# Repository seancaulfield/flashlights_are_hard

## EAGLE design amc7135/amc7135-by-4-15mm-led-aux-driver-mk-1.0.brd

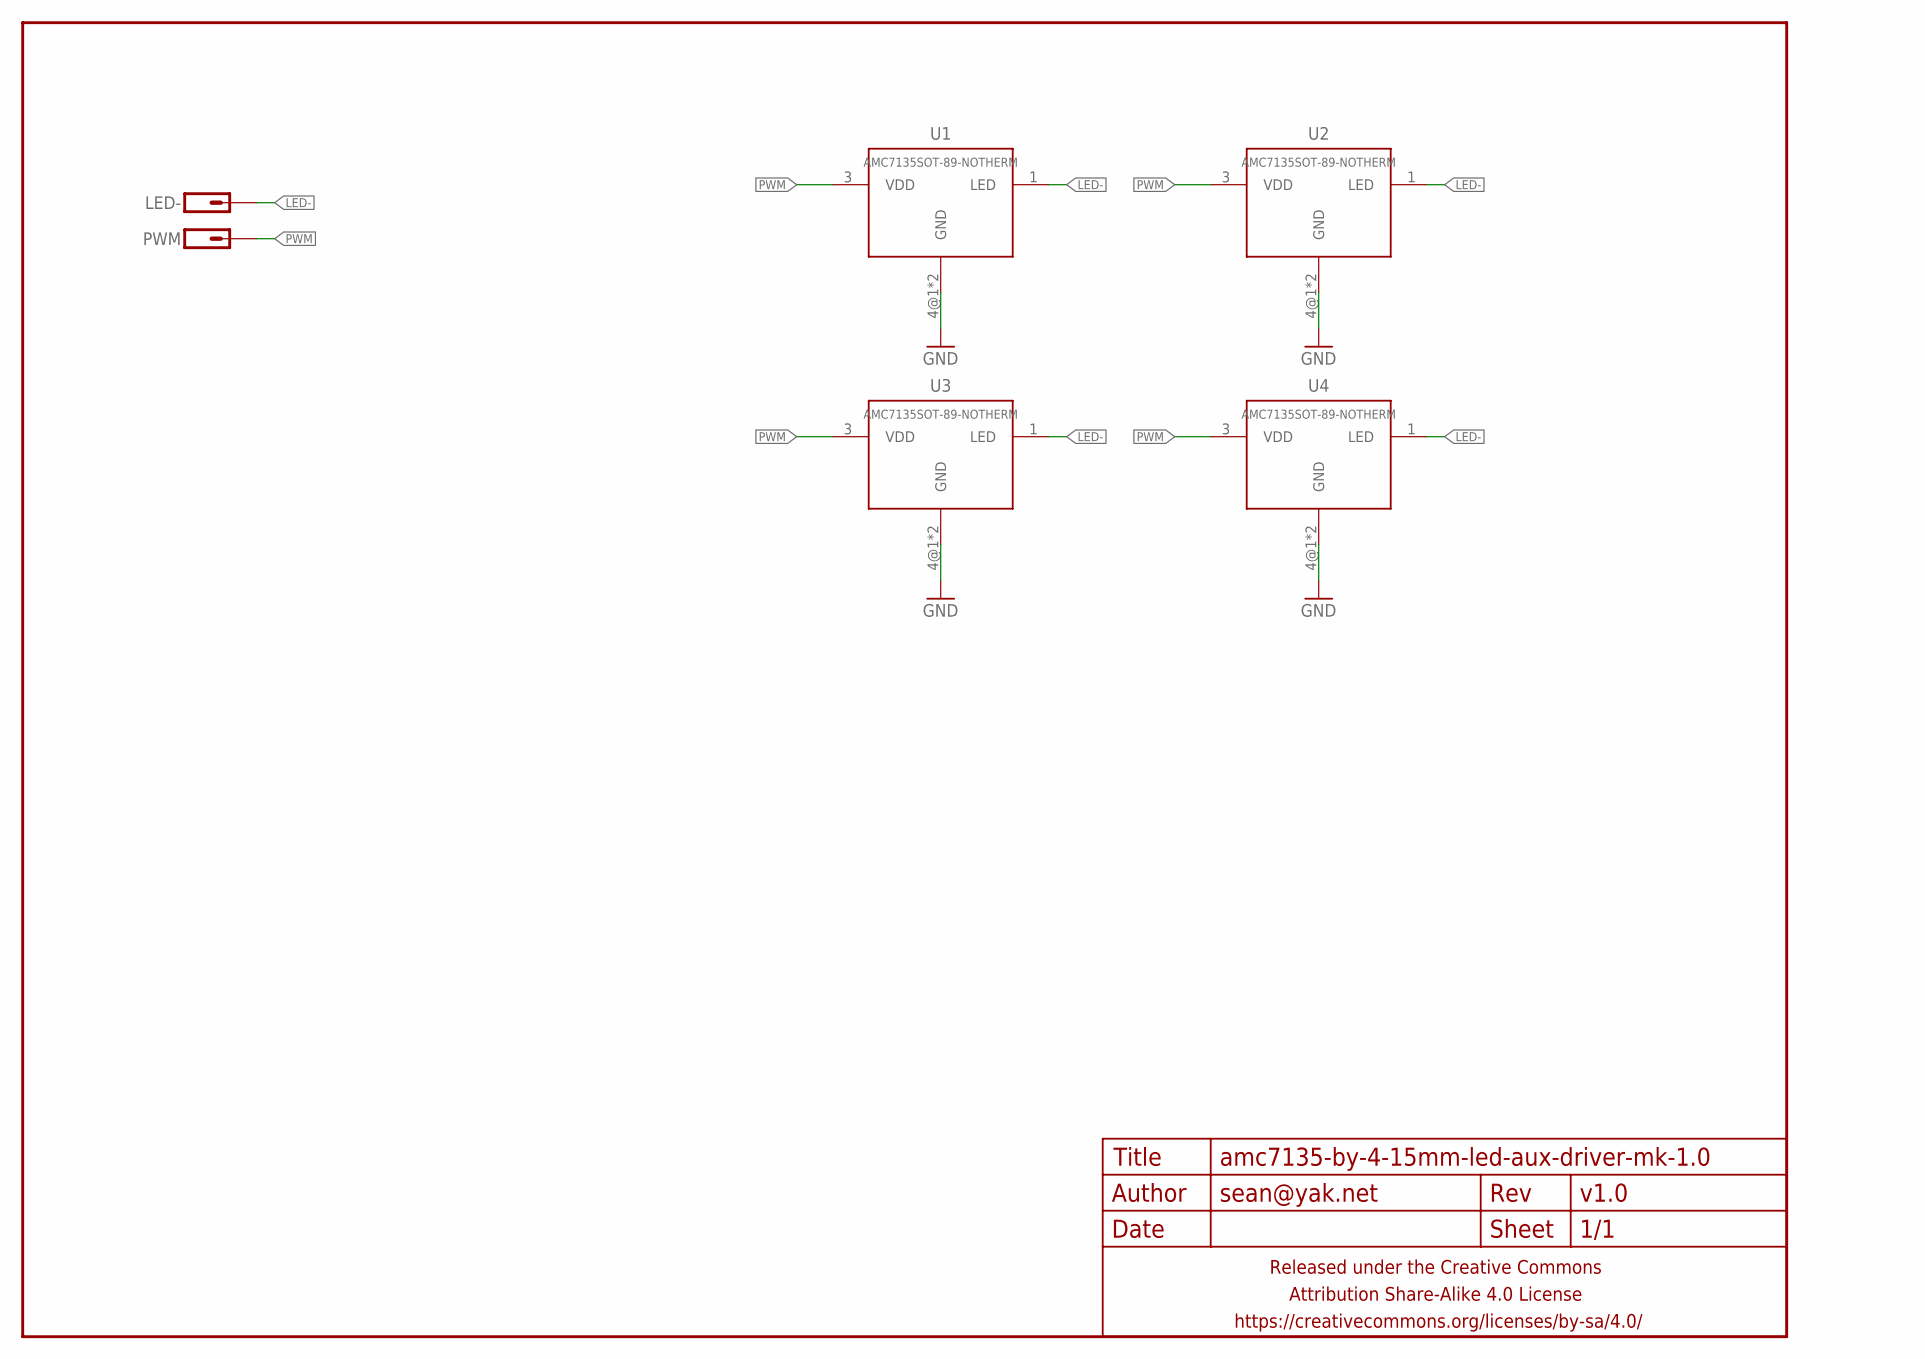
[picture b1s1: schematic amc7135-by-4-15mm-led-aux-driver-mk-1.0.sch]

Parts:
FRAME1: FRAME-LETTERNO_PACKAGE; DUMMY
LED-: M01SMD-1.25MM-DIA; 1X01-SMD-1.25MM-DIA-NS
PWM: M01SMD-1.25MM-DIA; 1X01-SMD-1.25MM-DIA-NS
U1, U2, U3, U4: AMC7135SOT-89-NOTHERM; SOT89-NOTHERM

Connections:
GND: U1.4@1 (GND), U1.4@2 (GND), U2.4@1 (GND), U2.4@2 (GND), U3.4@1 (GND), U3.4@2 (GND), U4.4@1 (GND), U4.4@2 (GND)
LED-: LED-.P$1, U1.1 (LED), U2.1 (LED), U3.1 (LED), U4.1 (LED)
PWM: PWM.P$1, U1.3 (VDD), U2.3 (VDD), U3.3 (VDD), U4.3 (VDD)

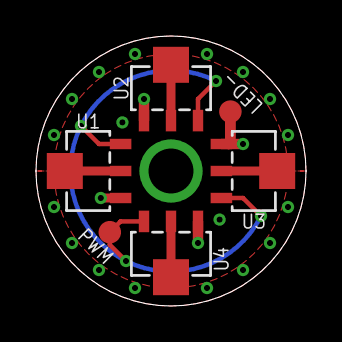
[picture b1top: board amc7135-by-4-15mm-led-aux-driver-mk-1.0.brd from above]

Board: 2 copper layers, 15.0 x 15.0 mm, 7 parts (0 on the bottom side), 3 nets.

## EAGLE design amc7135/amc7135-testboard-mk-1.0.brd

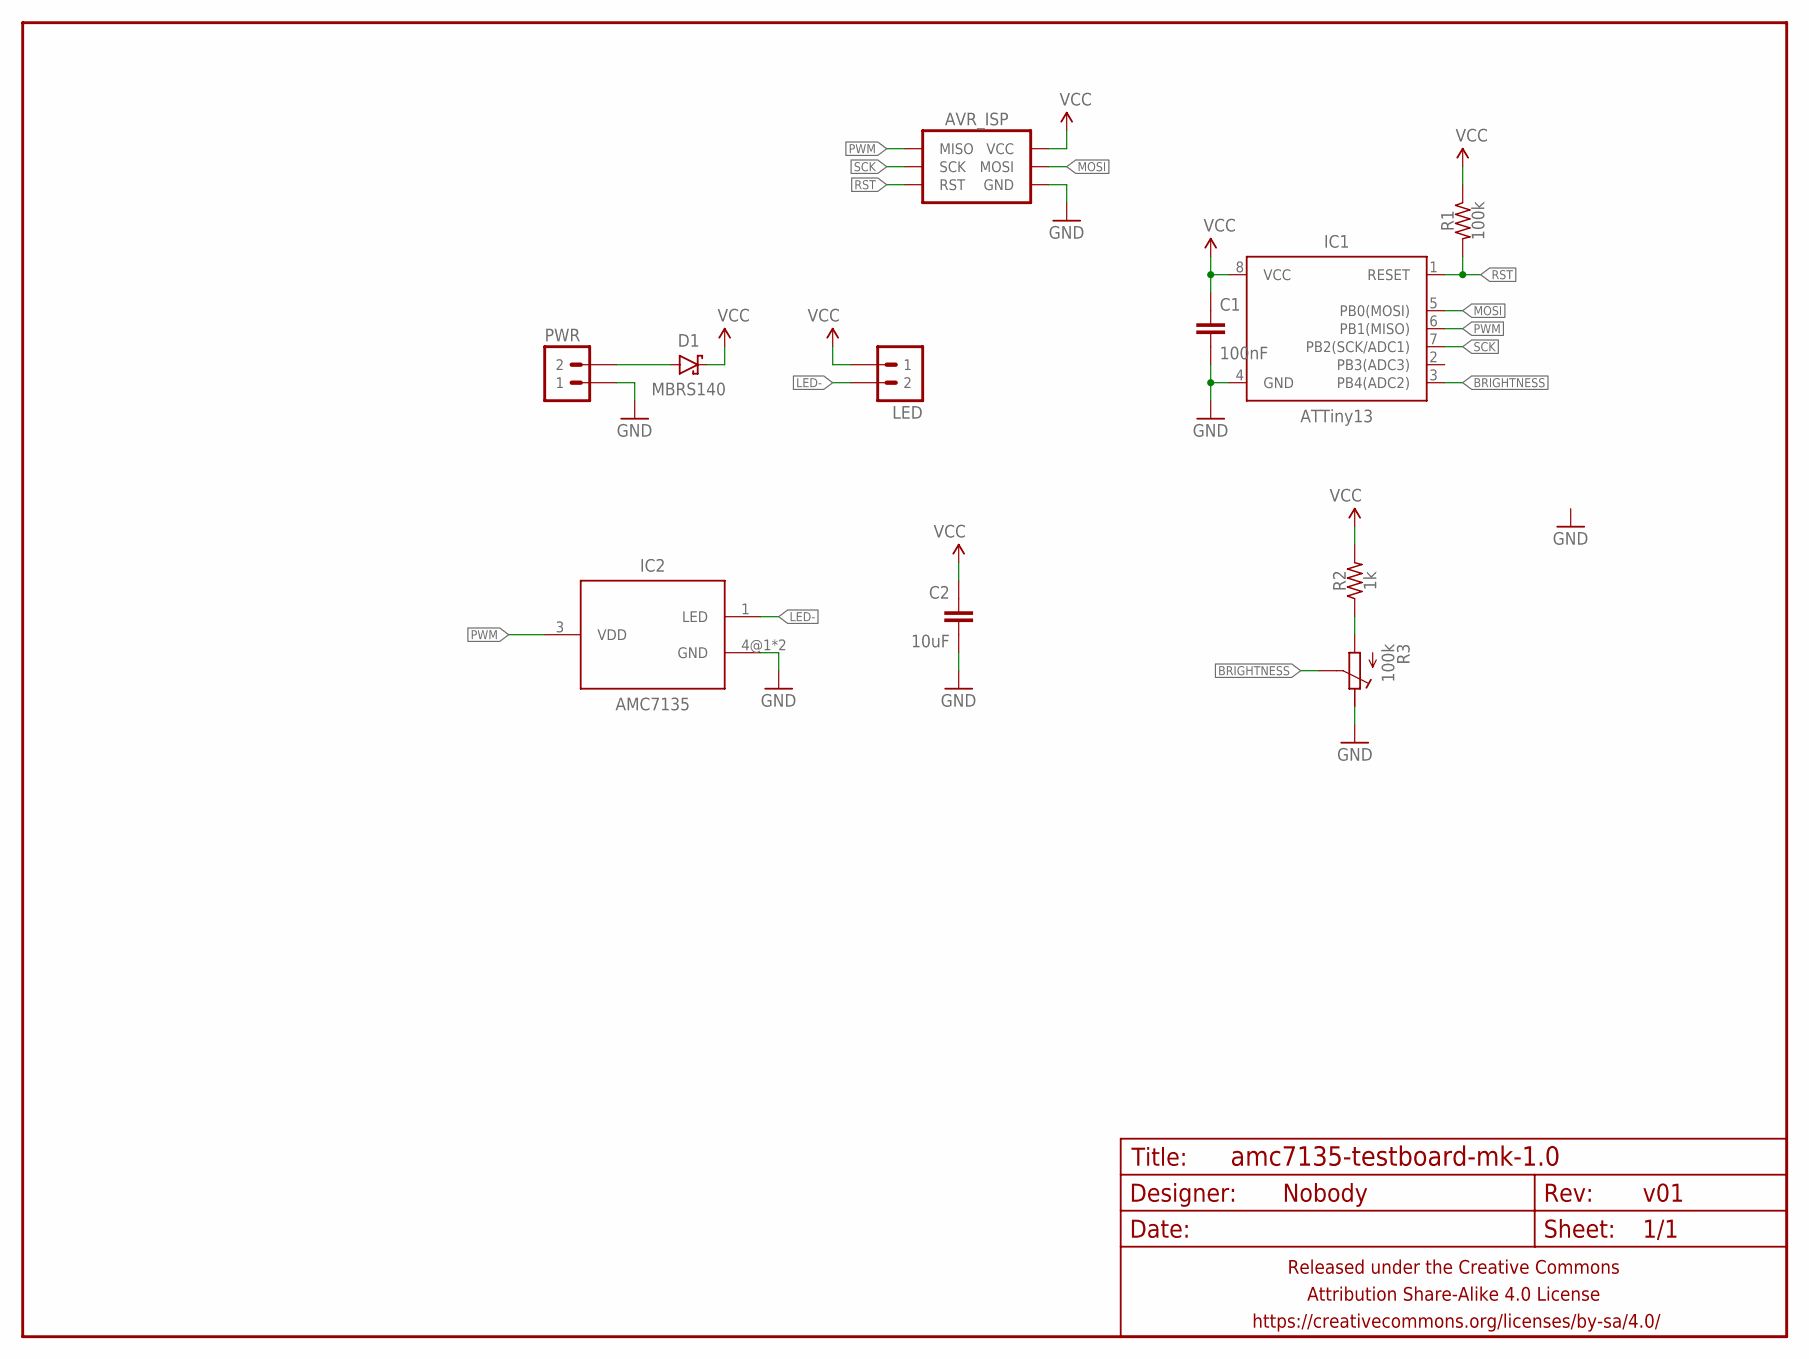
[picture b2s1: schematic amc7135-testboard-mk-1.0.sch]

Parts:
AVR_ISP: AVR_SPI_PRG_6SMD_TEST_POINTS; 2X3_SMD_TEST_POINTS
C1: 100nF; C0805
C2: 10uF; C0805
D1: MBRS140; SMA-DIODE-SCHOTTKY
FRAME1: FRAME-LETTERNO_PACKAGE; DUMMY
IC1: ATTiny13; SO08
IC2: AMC7135; SOT89-NOTHERM
LED: M02JST-PTH-RA-SMALLPADS; JST-2-PH-RA-PTH-SMALLPADS
PWR: M02JST-PTH-RA-SMALLPADS; JST-2-PH-RA-PTH-SMALLPADS
R1: 100k; R0805
R2: 1k; R0805
R3: 100k; EVM3Y

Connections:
BRIGHTNESS: IC1.3 (PB4(ADC2)), R3.S
GND: AVR_ISP.6 (GND), C1.2, C2.2, IC1.4 (GND), IC2.4@1 (GND), IC2.4@2 (GND), PWR.1, R3.E
LED-: IC2.1 (LED), LED.2
MOSI: AVR_ISP.4 (MOSI), IC1.5 (PB0(MOSI))
unnamed: R2.1, R3.A
unnamed: D1.A, PWR.2
PWM: AVR_ISP.1 (MISO), IC1.6 (PB1(MISO)), IC2.3 (VDD)
RST: AVR_ISP.5 (RST), IC1.1 (RESET), R1.2
SCK: AVR_ISP.3 (SCK), IC1.7 (PB2(SCK/ADC1))
VCC: AVR_ISP.2 (VCC), C1.1, C2.1, D1.C, IC1.8 (VCC), LED.1, R1.1, R2.2

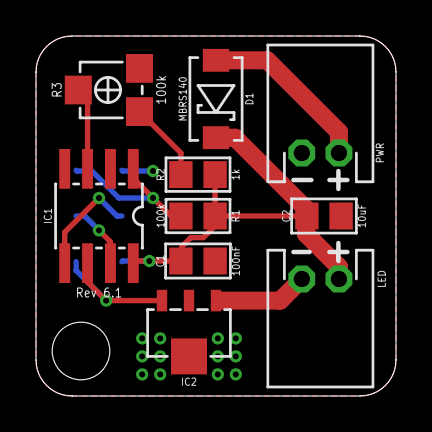
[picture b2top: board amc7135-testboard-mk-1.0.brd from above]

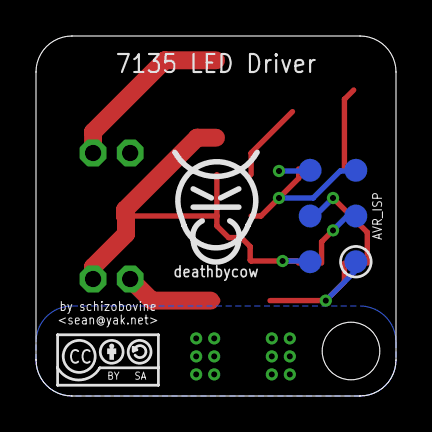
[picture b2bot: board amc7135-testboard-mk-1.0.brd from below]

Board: 2 copper layers, 20.0 x 20.0 mm, 14 parts (3 on the bottom side), 10 nets.

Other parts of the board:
U$1: CC-BY-SA-4.0-NO-URL
U$2: COW_SMALL

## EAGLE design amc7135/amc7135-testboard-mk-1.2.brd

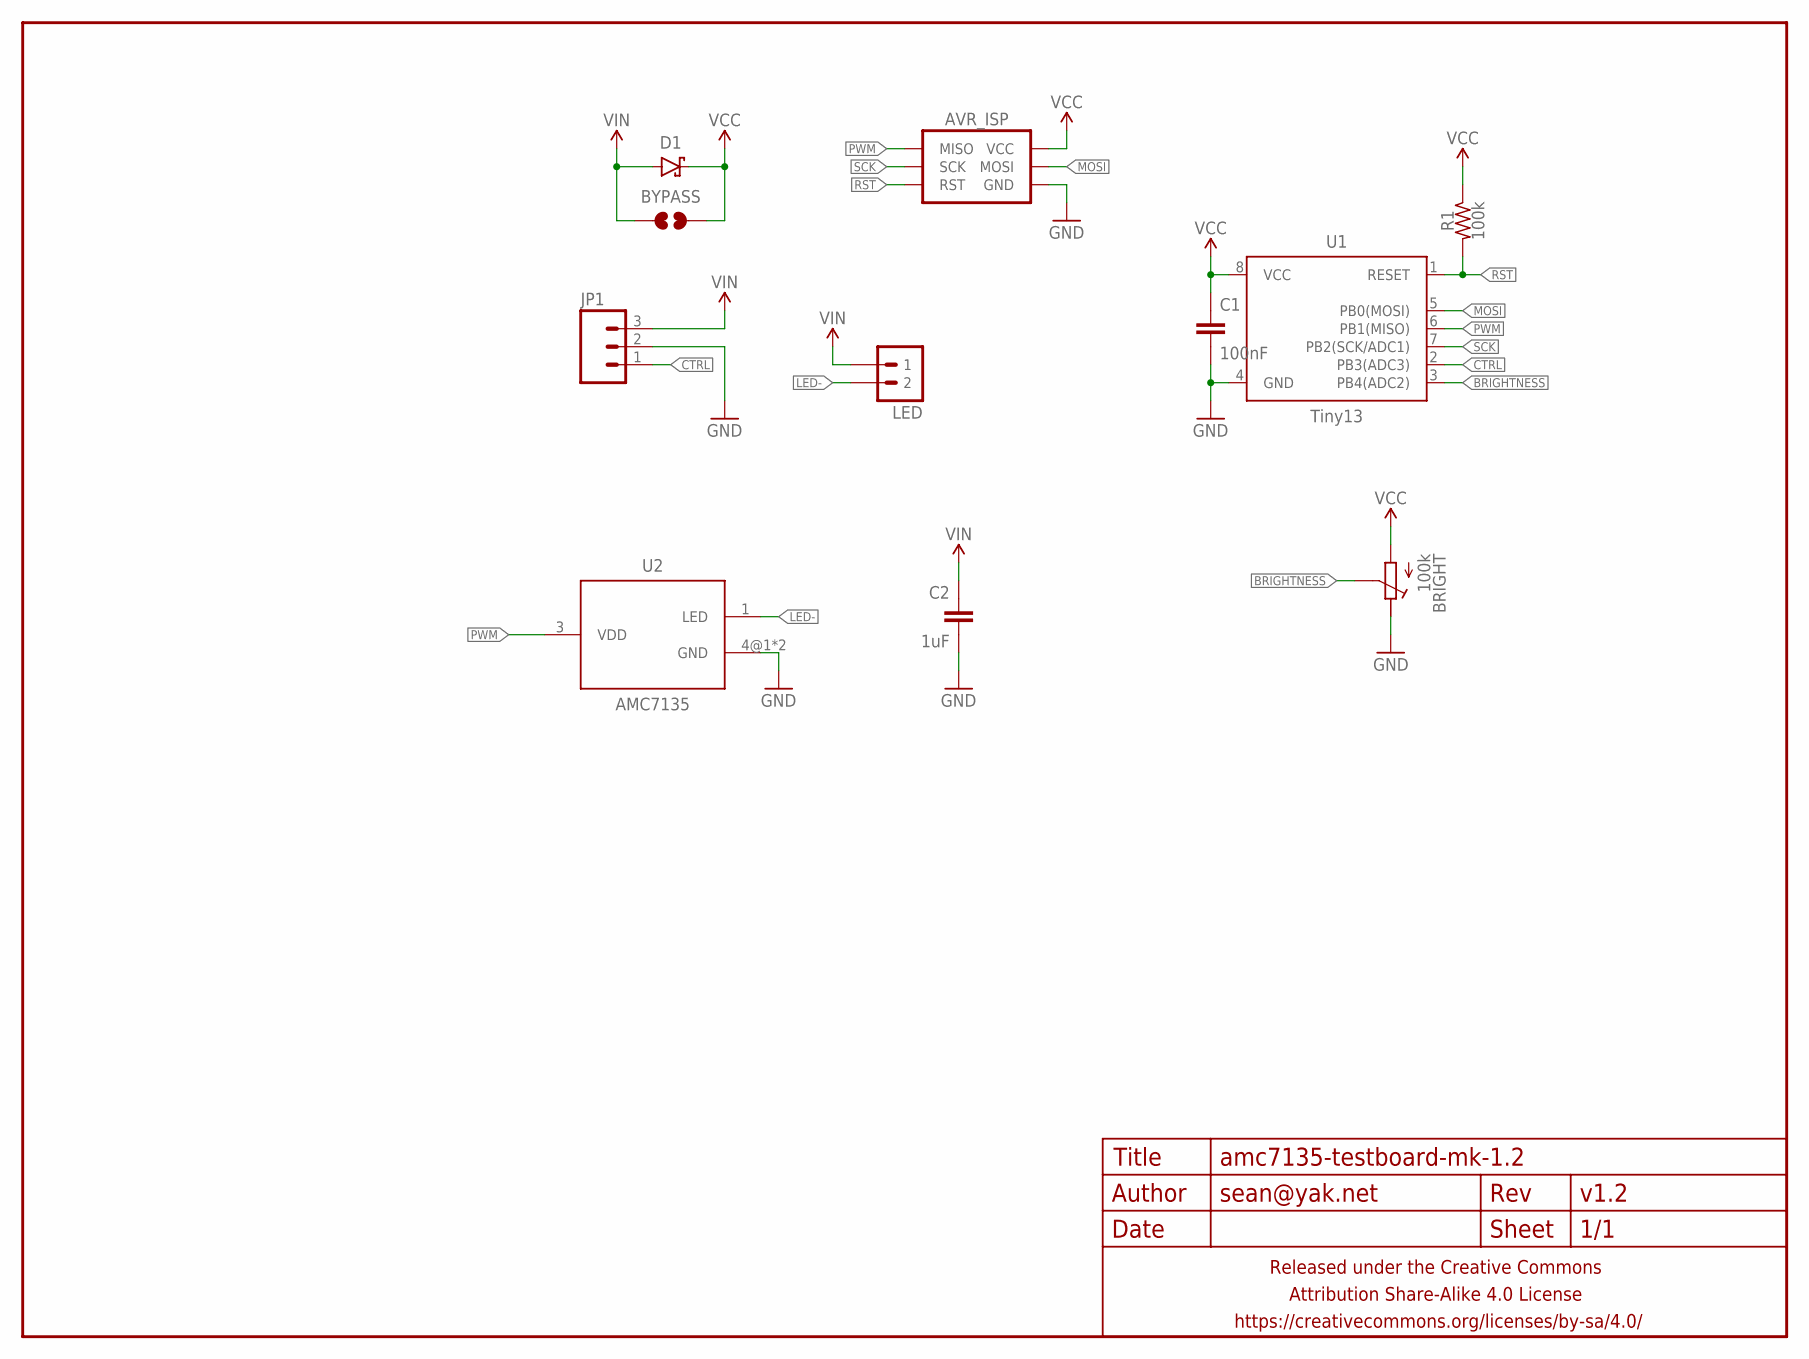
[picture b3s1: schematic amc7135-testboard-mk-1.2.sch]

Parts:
AVR_ISP: AVR_SPI_PRG_6SMD_TEST_POINTS; 2X3_SMD_TEST_POINTS
BRIGHT: 100k; EVM3Y
BYPASS: JUMPER-PAD-2-NOYES_SILK; PAD-JUMPER-2-NO_YES_SILK
C1: 100nF; C0603-TIGHTER
C2: 1uF; C0603-TIGHTER
D1: DIODE-SCHOTTKYSOD323; SOD323-SCHOTTKY
FRAME1: FRAME-LETTERNO_PACKAGE; DUMMY
JP1: M03PTH-CENTERED; 1X03-CENTERED
LED: M02PTH-CENTERED; 1X02-CENTER
R1: 100k; R0603-TIGHTER
U1: Tiny13; SO08
U2: AMC7135; SOT89-NOTHERM

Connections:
BRIGHTNESS: BRIGHT.S, U1.3 (PB4(ADC2))
CTRL: JP1.1, U1.2 (PB3(ADC3))
GND: AVR_ISP.6 (GND), BRIGHT.E, C1.2, C2.2, JP1.2, U1.4 (GND), U2.4@1 (GND), U2.4@2 (GND)
LED-: LED.2, U2.1 (LED)
MOSI: AVR_ISP.4 (MOSI), U1.5 (PB0(MOSI))
PWM: AVR_ISP.1 (MISO), U1.6 (PB1(MISO)), U2.3 (VDD)
RST: AVR_ISP.5 (RST), R1.2, U1.1 (RESET)
SCK: AVR_ISP.3 (SCK), U1.7 (PB2(SCK/ADC1))
VCC: AVR_ISP.2 (VCC), BRIGHT.A, BYPASS.2, C1.1, D1.C, R1.1, U1.8 (VCC)
VIN: BYPASS.1, C2.1, D1.A, JP1.3, LED.1

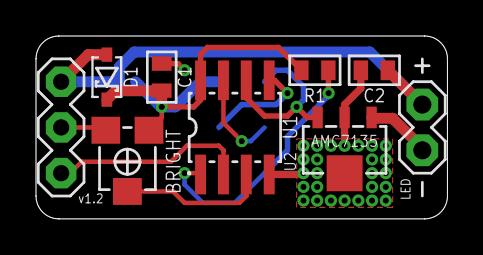
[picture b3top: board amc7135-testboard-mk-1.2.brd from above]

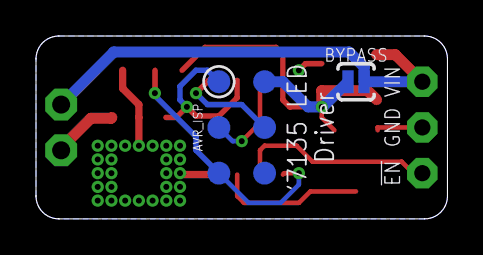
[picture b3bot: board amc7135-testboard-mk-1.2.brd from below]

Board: 2 copper layers, 22.9 x 10.2 mm, 12 parts (2 on the bottom side), 10 nets.

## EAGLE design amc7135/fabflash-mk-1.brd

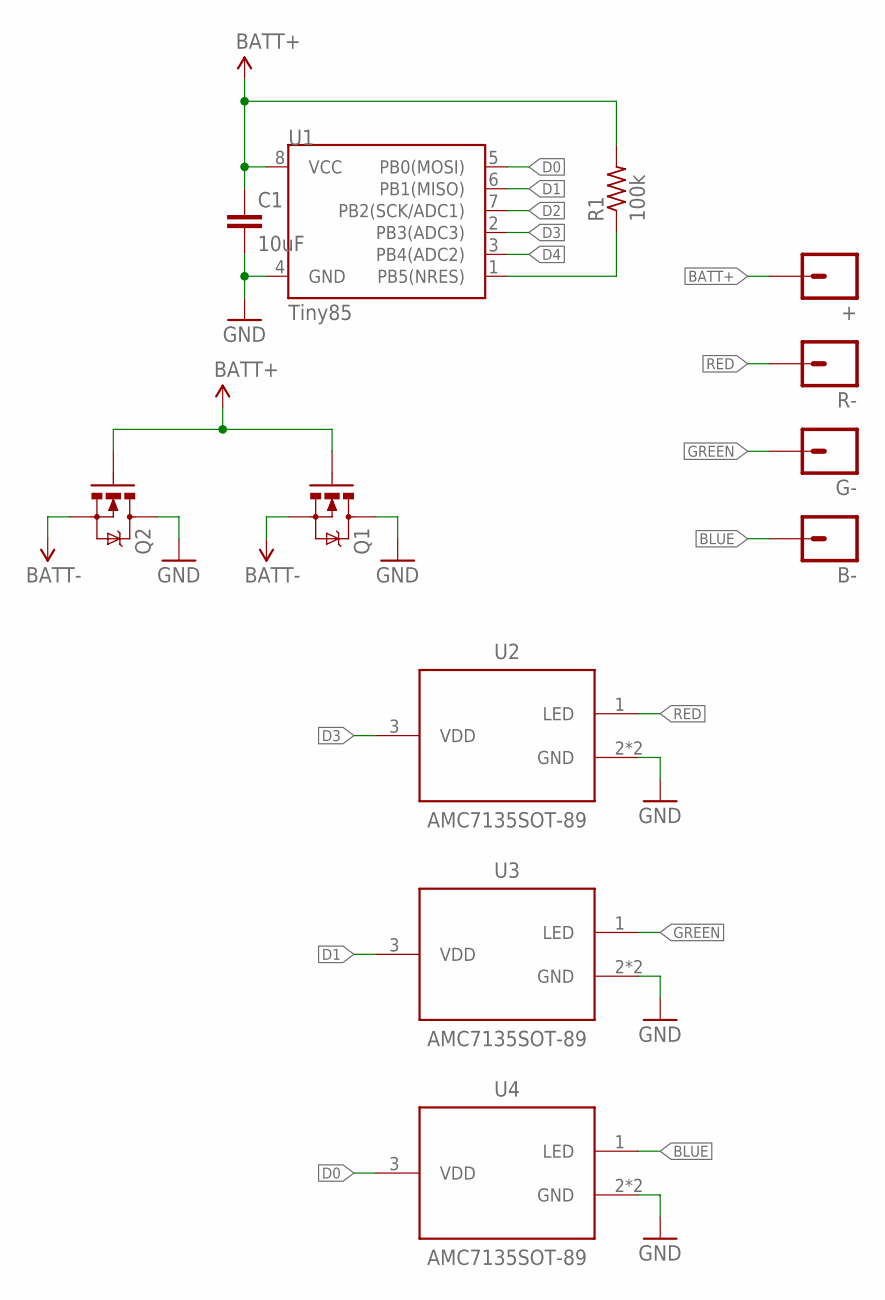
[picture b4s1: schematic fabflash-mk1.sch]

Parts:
+: M01PTH-1.2MM-NS; 1X01-1.2MM-NS
B-: M01PTH-1.2MM-NS; 1X01-1.2MM-NS
C1: 10uF; C0603
G-: M01PTH-1.2MM-NS; 1X01-1.2MM-NS
Q1, Q2: MOSFET-NCHANNELIRLML2502; SOT23
R1: 100k; R0603
R-: M01PTH-1.2MM-NS; 1X01-1.2MM-NS
U1: Tiny85; SO08-EIAJ
U2, U3, U4: AMC7135SOT-89; SOT89

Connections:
BATT+: +.P$1, C1.1, Q1.1 (G), Q2.1 (G), R1.2, U1.8 (VCC)
BATT-: Q1.2 (S), Q2.2 (S)
BLUE: B-.P$1, U4.1 (LED)
D0: U1.5 (PB0(MOSI)), U4.3 (VDD)
D1: U1.6 (PB1(MISO)), U3.3 (VDD)
D2: U1.7 (PB2(SCK/ADC1))
D3: U1.2 (PB3(ADC3)), U2.3 (VDD)
D4: U1.3 (PB4(ADC2))
GND: C1.2, Q1.3 (D), Q2.3 (D), U1.4 (GND), U2.2 (GND), U2.4 (GND), U3.2 (GND), U3.4 (GND), U4.2 (GND), U4.4 (GND)
GREEN: G-.P$1, U3.1 (LED)
RED: R-.P$1, U2.1 (LED)
RESET: R1.1, U1.1 (PB5(NRES))

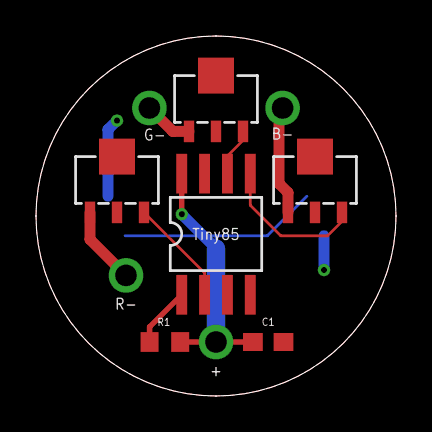
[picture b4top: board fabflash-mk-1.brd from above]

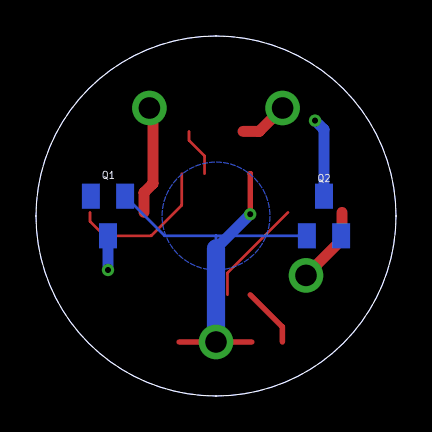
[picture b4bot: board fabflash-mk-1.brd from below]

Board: 2 copper layers, 20.0 x 20.0 mm, 12 parts (2 on the bottom side), 10 nets.

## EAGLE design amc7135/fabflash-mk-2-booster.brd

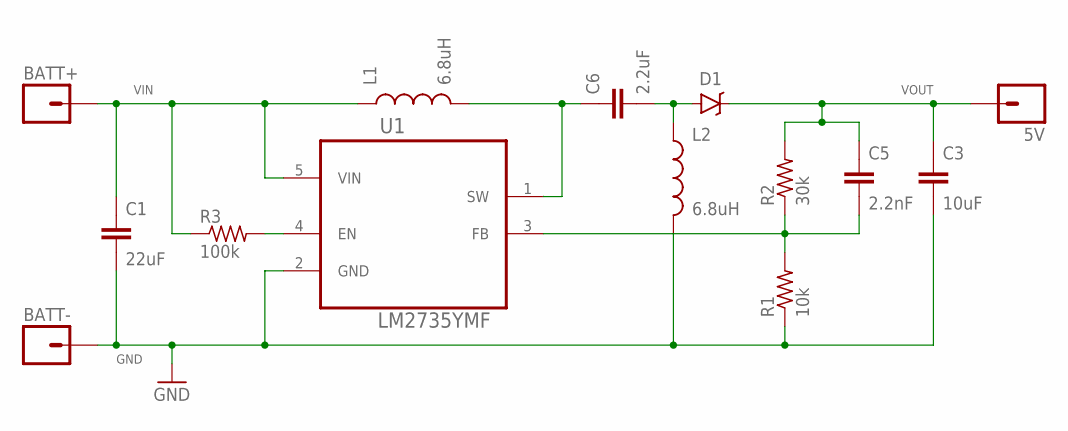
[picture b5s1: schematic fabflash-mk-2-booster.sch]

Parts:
5V: M01PTH-1.2MM; 1X01-1.2MM
BATT+: M01NOT-A-VIA-NOPE; 1X01_NOSILK_NOSTOP
BATT-: M01NOT-A-VIA-NOPE; 1X01_NOSILK_NOSTOP
C1: 22uF; C0805
C3: 10uF; C0805
C5: 2.2nF; C0805
C6: 2.2uF; C0805
D1: B340A; SMA-DIODE
L1, L2: 6.8uH; TAIYO-YUDEN-40XX
R1: 10k; R0805
R2: 30k; R0805
R3: 100k; R0805
U1: LM2735YMF; SOT95P285X110-5N

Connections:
GND: BATT-.P$1, C1.2, C3.2, L2.2, R1.1, U1.2 (GND)
unnamed: C6.1, L1.2, U1.1 (SW)
unnamed: R3.2, U1.4 (EN)
unnamed: C6.2, D1.A, L2.1
unnamed: C5.2, R1.2, R2.1, U1.3 (FB)
VIN: BATT+.P$1, C1.1, L1.1, R3.1, U1.5 (VIN)
VOUT: 5V.P$1, C3.1, C5.1, D1.C, R2.2

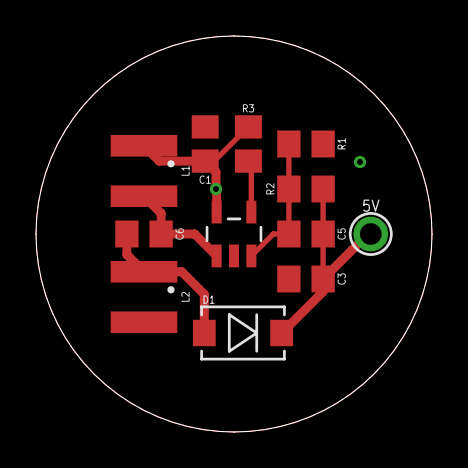
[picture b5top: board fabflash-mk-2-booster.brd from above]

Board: 2 copper layers, 22.0 x 22.0 mm, 14 parts (0 on the bottom side), 7 nets.

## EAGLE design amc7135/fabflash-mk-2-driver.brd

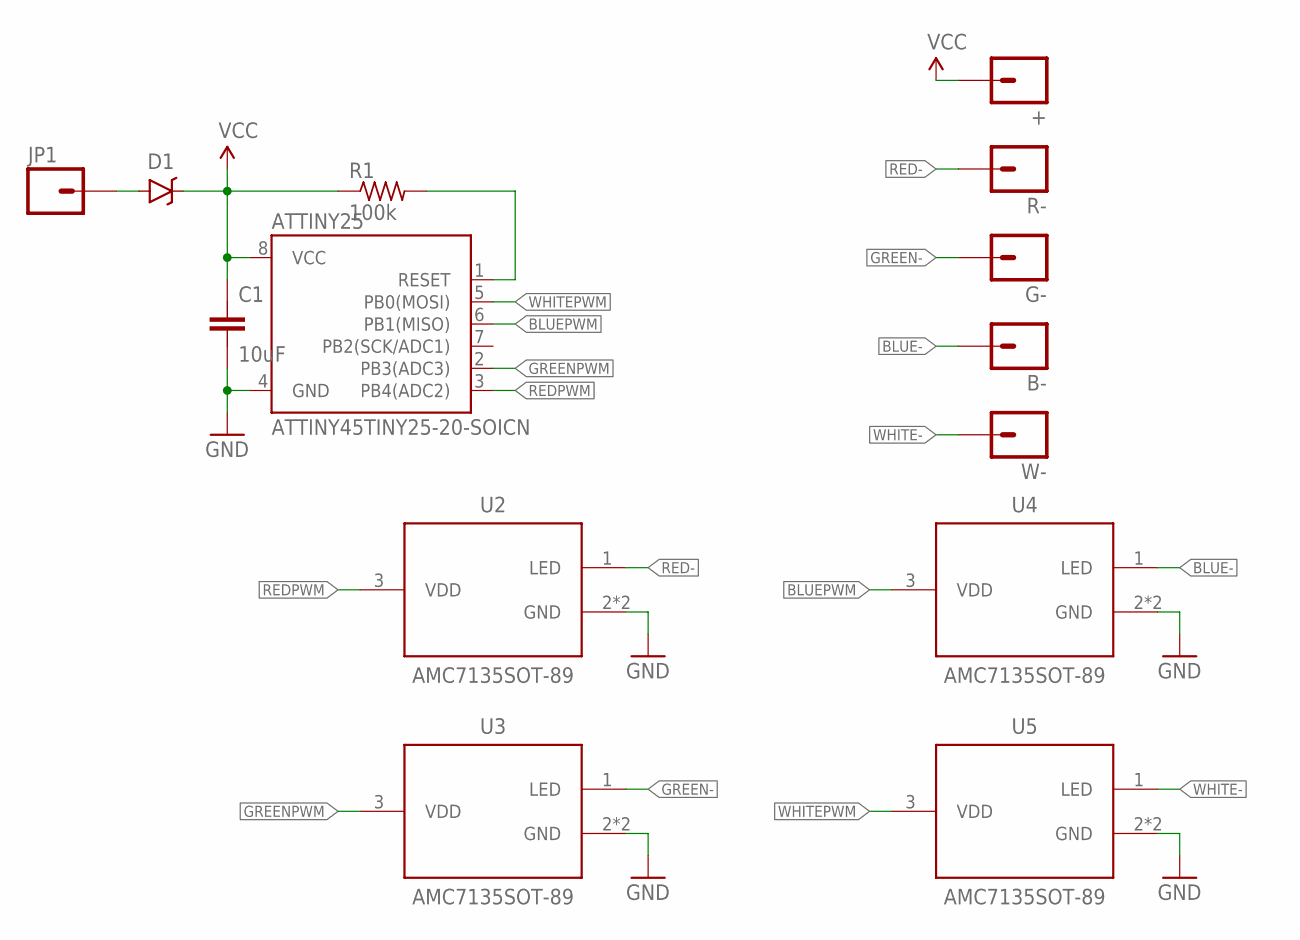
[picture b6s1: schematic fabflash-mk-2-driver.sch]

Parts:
+: M01PTH-0.9MM; 1X01-0.9MM-NS
ATTINY25: ATTINY45TINY25-20-SOICN; SO08
B-: M01PTH-0.9MM; 1X01-0.9MM-NS
C1: 10uF; C0805
D1: MBRA140; SMA-DIODE
G-: M01PTH-0.9MM; 1X01-0.9MM-NS
JP1: M01NOT-A-VIA-NOPE; 1X01_NOSILK_NOSTOP
R1: 100k; R0805
R-: M01PTH-0.9MM; 1X01-0.9MM-NS
U2, U3, U4, U5: AMC7135SOT-89; SOT89
W-: M01PTH-0.9MM; 1X01-0.9MM-NS

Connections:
BATT+: D1.A, JP1.P$1
BLUE-: B-.1, U4.1 (LED)
BLUEPWM: ATTINY25.6 (PB1(MISO)), U4.3 (VDD)
GND: ATTINY25.4 (GND), C1.2, U2.2 (GND), U2.4 (GND), U3.2 (GND), U3.4 (GND), U4.2 (GND), U4.4 (GND), U5.2 (GND), U5.4 (GND)
GREEN-: G-.1, U3.1 (LED)
GREENPWM: ATTINY25.2 (PB3(ADC3)), U3.3 (VDD)
RED-: R-.1, U2.1 (LED)
REDPWM: ATTINY25.3 (PB4(ADC2)), U2.3 (VDD)
RESET: ATTINY25.1 (RESET), R1.2
VCC: +.1, ATTINY25.8 (VCC), C1.1, D1.C, R1.1
WHITE-: U5.1 (LED), W-.1
WHITEPWM: ATTINY25.5 (PB0(MOSI)), U5.3 (VDD)

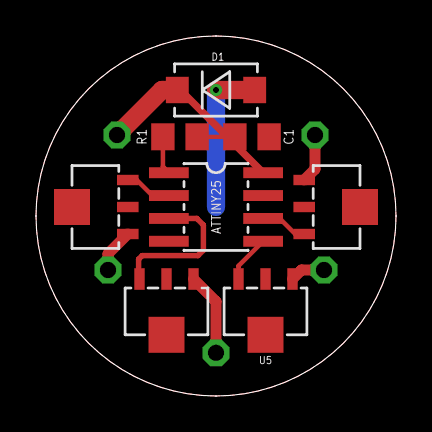
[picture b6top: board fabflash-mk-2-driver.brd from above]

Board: 2 copper layers, 20.0 x 20.0 mm, 14 parts (0 on the bottom side), 12 nets.

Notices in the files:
parts and their libraries:
a_parts: Released under the Creative Commons Attribution Share-Alike 4.0 License
a_parts: https://creativecommons.org/licenses/by-sa/4.0
a_parts: Released under the Creative Commons
